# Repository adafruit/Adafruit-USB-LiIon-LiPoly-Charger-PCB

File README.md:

## Adafruit USB LiIon/LiPoly Charger PCB
<a href="http://www.adafruit.com/products/259"><br/>
Click here to purchase one from the Adafruit shop</a>

This is a Lithium Ion and Lithium Polymer battery charger based on the MCP73833. It uses a USB mini-B for connection to any computer or 'USB wall adapter'. Charging is performed in three stages: first a preconditioning charge, then a constant-current fast charge and finally a constant-voltage trickle charge to keep the battery topped-up. The fast-charge current is 500mA by default, but is easily adjustable from 100mA up to 1000mA by soldering a through-hole resistor on-board.

This board is great for DIY projects because it has 3 indicator LEDs - one for power, one for charging status and a third that indicates when charging is complete. Keep the battery connected to the charger and pass power through the additional JST connector using the included cable!

These are the Eagle CAD files for the Adafruit USB LiIon/LiPoly Charger

Format is EagleCAD schematic and board layout

### License

Adafruit invests time and resources providing this open source design, please support Adafruit and open-source hardware by purchasing products from [Adafruit](https://www.adafruit.com)!

All text above must be included in any redistribution

Designed by Limor Fried/Ladyada for Adafruit Industries.
Creative Commons Attribution/Share-Alike, all text above must be included in any redistribution. 
See license.txt for additional information.

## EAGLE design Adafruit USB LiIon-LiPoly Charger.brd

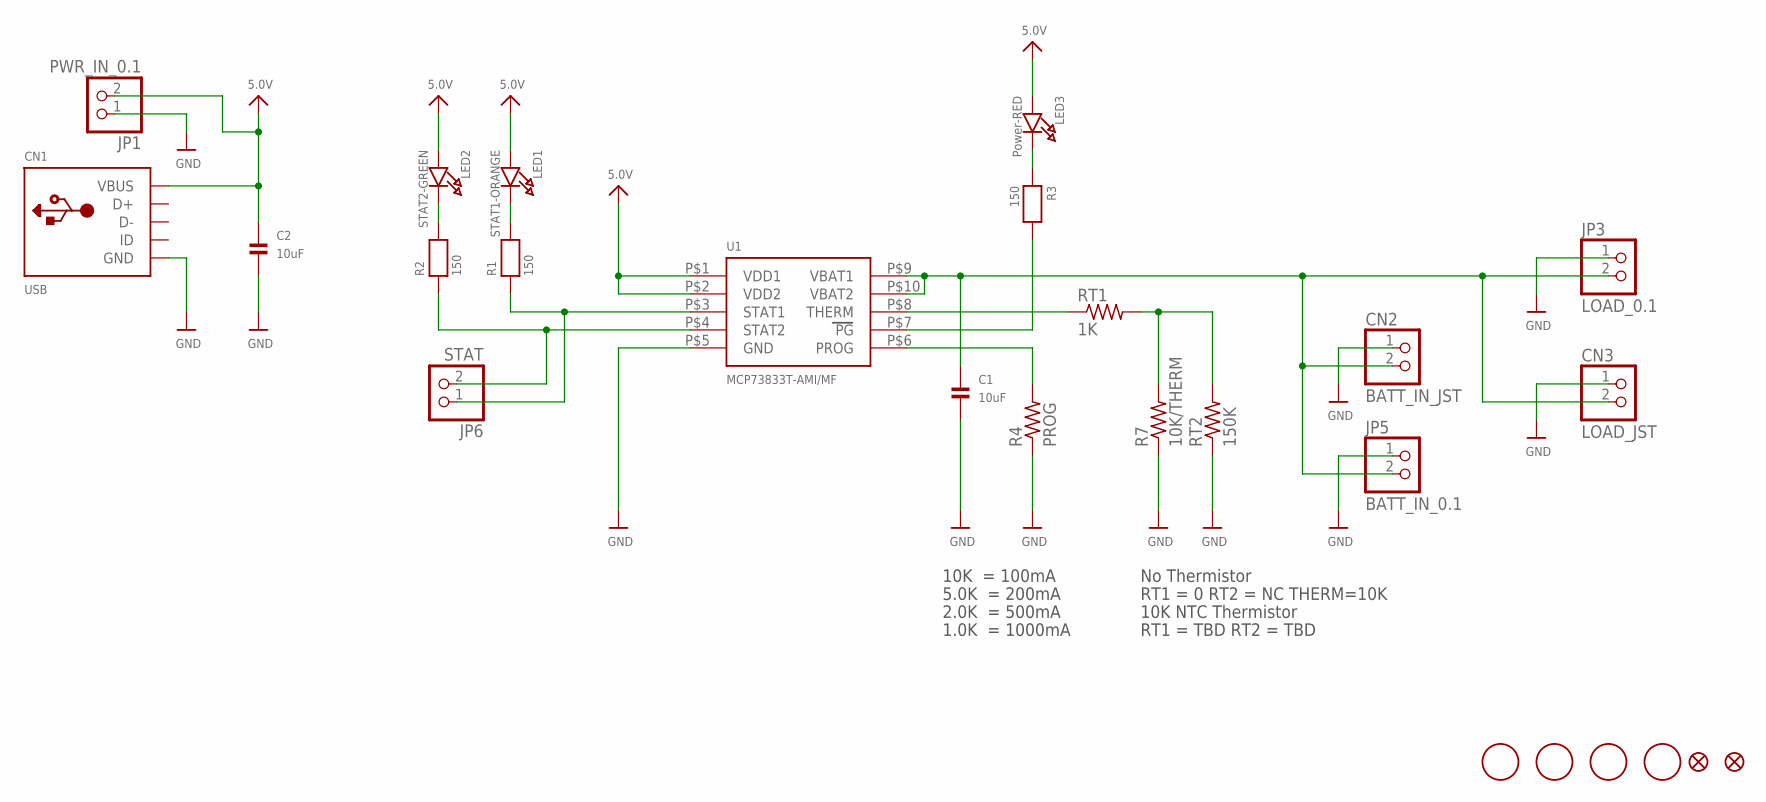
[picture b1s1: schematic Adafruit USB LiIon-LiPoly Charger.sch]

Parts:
C1, C2: 10uF; 0805
CN1: USB; USB-MINIB_LARGER
CN2: BATT_IN_JST; JSTPH2
CN3: LOAD_JST; JSTPH2
JP1: PWR_IN_0.1; 1X02_OVAL
JP2, JP4: FIDUCIAL1.5X3; FIDUCIAL-1X2.5
JP3: LOAD_0.1; 1X02_OVAL
JP5: BATT_IN_0.1; 1X02_OVAL
JP6: STAT; 1X02_OVAL
LED1: STAT1-ORANGE; CHIPLED_0805
LED2: STAT2-GREEN; CHIPLED_0805
LED3: Power-RED; CHIPLED_0805
R1, R2, R3: 150; 0805
R4: PROG; 0805-THM
R7: 10K/THERM; 0805-THM
RT1: 1K; R0805
RT2: 150K; R0805
U1: MCP73833T-AMI/MF; DFN10_3X3MM
U$11, U$16, U$18, U$19: MOUNTINGHOLE2.0; MOUNTINGHOLE_2.0_PLATED

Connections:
5.0V: C2.1, CN1.VBUS, JP1.2, LED1.A, LED2.A, LED3.A, U1.P$1 (VDD1), U1.P$2 (VDD2)
BATT: C1.1, CN2.2, CN3.2, JP3.2, JP5.2, U1.P$9 (VBAT1), U1.P$10 (VBAT2)
GND: C1.2, C2.2, CN1.GND, CN2.1, CN3.1, JP1.1, JP3.1, JP5.1, R4.1, R7.1, RT2.1, U1.P$5 (GND)
unnamed: LED1.C, R1.2
unnamed: LED2.C, R2.2
unnamed: JP6.1, R1.1, U1.P$3 (STAT1)
unnamed: JP6.2, R2.1, U1.P$4 (STAT2)
unnamed: RT1.1, U1.P$8 (THERM)
unnamed: R3.2, U1.P$7 (PG)
unnamed: R7.2, RT1.2, RT2.2
unnamed: LED3.C, R3.1
unnamed: R4.2, U1.P$6 (PROG)

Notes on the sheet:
10K = 100mA
5.0K = 200mA
2.0K = 500mA
1.0K = 1000mA
No Thermistor
RT1 = 0 RT2 = NC THERM=10K
10K NTC Thermistor
RT1 = TBD RT2 = TBD

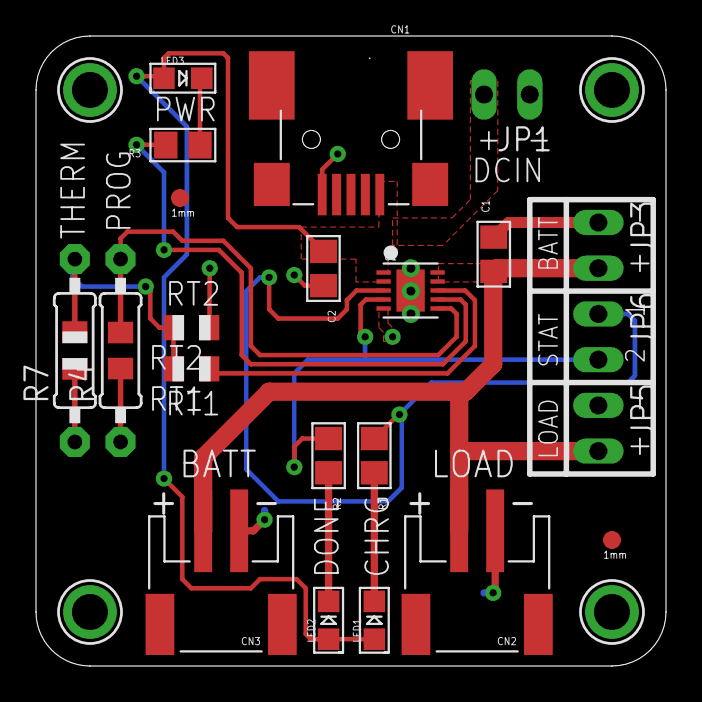
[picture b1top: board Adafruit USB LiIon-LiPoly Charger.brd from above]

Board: 2 copper layers, 35.0 x 35.0 mm, 27 parts (1 on the bottom side), 12 nets.

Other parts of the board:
U$14: ADAFRUIT200MIL

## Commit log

2014-12-21 init
2026-06-02 update file format to XML
